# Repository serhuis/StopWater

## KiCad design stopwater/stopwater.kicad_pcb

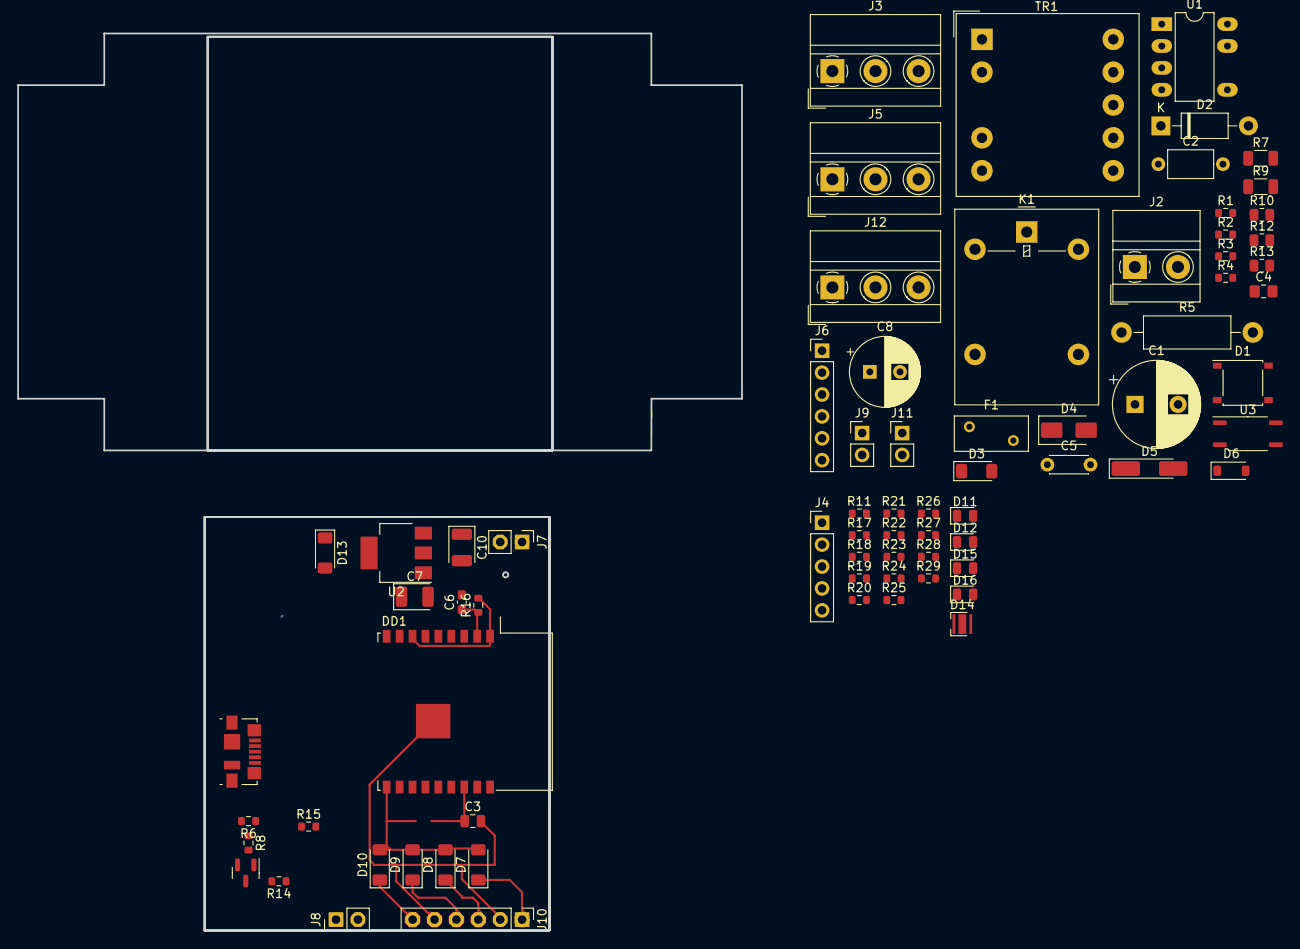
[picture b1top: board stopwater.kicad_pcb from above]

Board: 2 copper layers, 84.0 x 104.1 mm, 74 parts (0 on the bottom side), 57 nets.

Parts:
C1: 10u 400v; CP_Radial_D10.0mm_P5.00mm
C2: 2.2n; C_Axial_L5.1mm_D3.1mm_P7.50mm_Horizontal
C3: 1u; C_0805_2012Metric
C4: C_Polarized_Small; C_0805_2012Metric_Pad1.18x1.45mm_HandSolder
C5: C_Polarized_Small; C_Disc_D4.3mm_W1.9mm_P5.00mm
C6: 0.1u; C_0603_1608Metric_Pad1.08x0.95mm_HandSolder
C7, C10: 10u; CP_EIA-3528-15_AVX-H
C8: 200u 16v; CP_Radial_D8.0mm_P3.50mm
D1: ABS10; Diode_Bridge_Diotec_ABS
D2: 1N4937; D_DO-41_SOD81_P10.16mm_Horizontal
D3, D7, D8, D9, D10, D13: LL4148; D_MiniMELF
D4: SS14; D_SMA
D5: 8v2; D_MiniMELF_Handsoldering
D6: MMSD4148; D_SOD-123
D11, D12: "SENS_1"; LED_0805_2012Metric
D14: LED_Dual_AAK; LED_Cree-XB
D15: "SENS_3"; LED_0805_2012Metric
D16: "SENS_4"; LED_0805_2012Metric
DD1: ESP32c3-WROOM-02; ESP-WROOM-02
F1: 8.2R; Fuse_BelFuse_0ZRE0005FF_L8.3mm_W3.8mm
J1: USB_B_Micro; USB_Micro-B_Molex_47346-0001
J2: ~220; TerminalBlock_MetzConnect_Type011_RT05502HBWC_1x02_P5.00mm_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
J3, J5, J12: Out; TerminalBlock_MetzConnect_Type011_RT05503HBWC_1x03_P5.00mm_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
J4: Conn_01x05; PinHeader_1x05_P2.54mm_Vertical
J6: Conn_01x06_Pin; PinHeader_1x06_P2.54mm_Vertical
J7, J9: Conn_01x02_Pin; PinHeader_1x02_P2.54mm_Vertical
J8, J11: Conn_01x02_Socket; PinHeader_1x02_P2.54mm_Vertical
J10: Conn_01x06_Socket; PinHeader_1x06_P2.54mm_Vertical
K1: G5LE-1; Relay_SPDT_Omron-G5LE-1
Q1: BC847; SOT-23
R1, R2, R3, R4, R14: 3.3k; R_0603_1608Metric
R5: 200k; R_Axial_DIN0411_L9.9mm_D3.6mm_P15.24mm_Horizontal
R6: 330; R_0603_1608Metric
R7, R9: 1M; R_1206_3216Metric
R8, R11, R16, R17, R18, R19, R20, R21, R22, R23, R24, R25, R26, R27, R28, R29: 10k; R_0603_1608Metric
R10: 10k; R_0805_2012Metric
R12: 330; R_0805_2012Metric
R13: 680; R_0805_2012Metric
R15: 1k; R_0603_1608Metric
TR1: FAT_74082
U1: TNY268P; PowerIntegrations_PDIP-8B
U2: LD1117S33TR_SOT223; SOT-223-3_TabPin2
U3: TLP181; SOIC-4_4.55x3.7mm_P2.54mm

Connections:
+3.3V: C3.1, C7.1, DD1.1 (3V3), R11.1, R16.2, R17.1, R18.1, R19.1, R20.1, R21.1, R22.1, R23.1, R24.1, R25.1, R26.1, R27.1, R28.1, R29.1, U2.2 (VO)
+12V: C8.1 (plus), D4.1 (K), D5.1 (K), D6.1 (K), D6.2 (A), J8.1, J9.1, J9.2, J11.1, K1.2, K1.5, R1.1, R2.1, R3.1, R4.1
/+12: C10.1, D13.1 (K), J7.1, U2.3 (VI)
/IO_0: D7.2 (A), DD1.18 (IO0), R17.2
/IO_1: D8.2 (A), DD1.17 (IO1), R18.2
/IO_2: DD1.16 (IO2), R19.2
/IO_3: D9.2 (A), DD1.15 (IO3), R20.2
/IO_4: DD1.3 (IO4), R6.2, R15.2, R21.2
/IO_5: D11.1 (K), DD1.4 (IO5), R22.2
/IO_6: D12.1 (K), DD1.5 (IO6), R23.2
/IO_7: D15.1 (K), DD1.6 (IO7), R24.2
/IO_8: D16.1 (K), DD1.7 (IO8), R25.2
/IO_9: DD1.8 (IO9), J4.2, R26.2
/IO_10: D10.2 (A), DD1.10 (IO10)
/SENSOR_1: D7.1 (K), J10.1
/SENSOR_2: D8.1 (K), J10.3
/SENSOR_3: D9.1 (K), J10.4
/SENSOR_4: D10.1 (K), J10.6
/USB_DN: DD1.13 (IO18), J1.2 (D-)
/USB_DP: DD1.14 (IO19), J1.3 (D+)
/power/SENSOR_1: J3.1, J6.1, R1.2
/power/SENSOR_2: J3.3, J6.3, R2.2, R3.2
/power/SENSOR_3: J5.1, J6.4
/power/SENSOR_4: J5.3, J6.6, R4.2
GND: C3.2, C6.2, C7.2, C10.2, D14.3 (K), DD1.9 (GND), DD1.19 (GND), J1.5 (GND), J1.6 (Shield), J3.2, J4.3, J5.2, J6.2, J6.5, J7.2, J10.2, J10.5, J11.2, Q1.2 (E), R8.1, R13.2, U2.1 (GND), U3.3
unnamed: C1.2 (minus), C4.2 (minus), D1.2 (-), TR1.1, U1.2 (S), U1.3 (S), U1.7 (S), U1.8 (S), U3.4
unnamed: C1.1 (plus), C2.2, C5.2 (minus), D1.1 (+), R5.2, R7.2, TR1.5
unnamed: C4.1 (plus), R10.2, U1.1 (BP)
unnamed: C5.1 (plus), C8.2 (minus), TR1.10
unnamed: D1.3, F1.2
unnamed: D2.2 (A), TR1.4, U1.5 (D)
unnamed: C2.1, D2.1 (K), R5.1
unnamed: D3.2 (A), TR1.2
unnamed: D3.1 (K), R10.1
unnamed: D4.2 (A), TR1.6
unnamed: D5.2 (A), R12.2
unnamed: D11.2 (A), R11.2
unnamed: D12.2 (A), R27.2
unnamed: D13.2 (A), J1.1 (VBUS)
unnamed: D14.1 (A1), R15.1
unnamed: D14.2 (A2), R14.1
unnamed: D15.2 (A), R28.2
unnamed: D16.2 (A), R29.2
unnamed: C6.1, DD1.2 (EN), J4.1, R16.1
unnamed: DD1.11 (RXD), J4.4
unnamed: DD1.12 (TXD), J4.5
unnamed: F1.1, J2.1
unnamed: D1.4, J2.2
unnamed: J8.2, Q1.3 (C), R14.2
unnamed: J12.1, K1.4
unnamed: J12.2, K1.1
unnamed: J12.3, K1.3
unnamed: Q1.1 (B), R6.1, R8.2
unnamed: R7.1, R9.2
unnamed: R12.1, R13.1, U3.1
unnamed: TR1.7, TR1.9
unnamed: R9.1, U1.4 (EN/UV), U3.6

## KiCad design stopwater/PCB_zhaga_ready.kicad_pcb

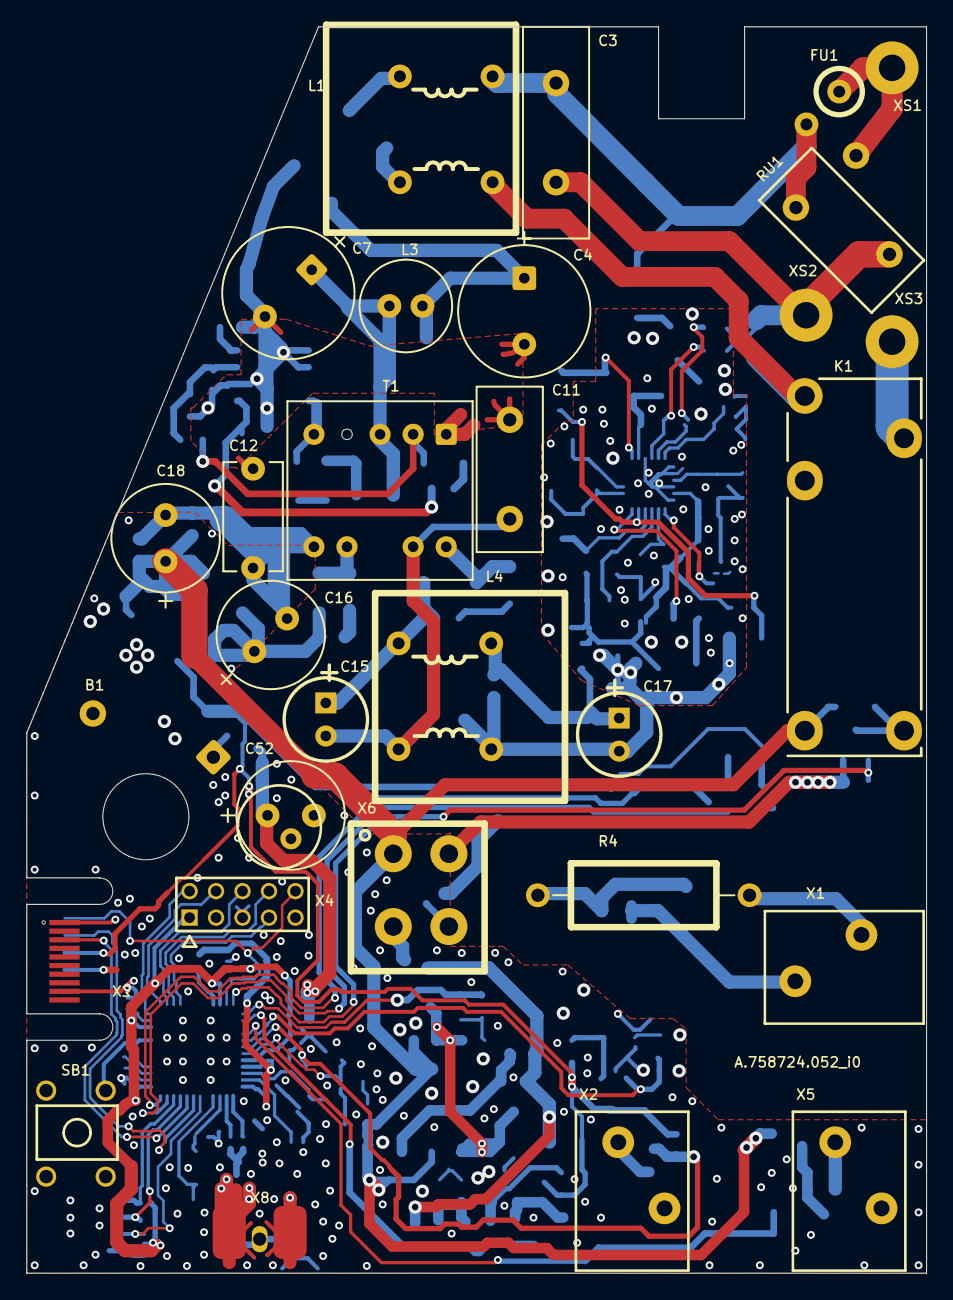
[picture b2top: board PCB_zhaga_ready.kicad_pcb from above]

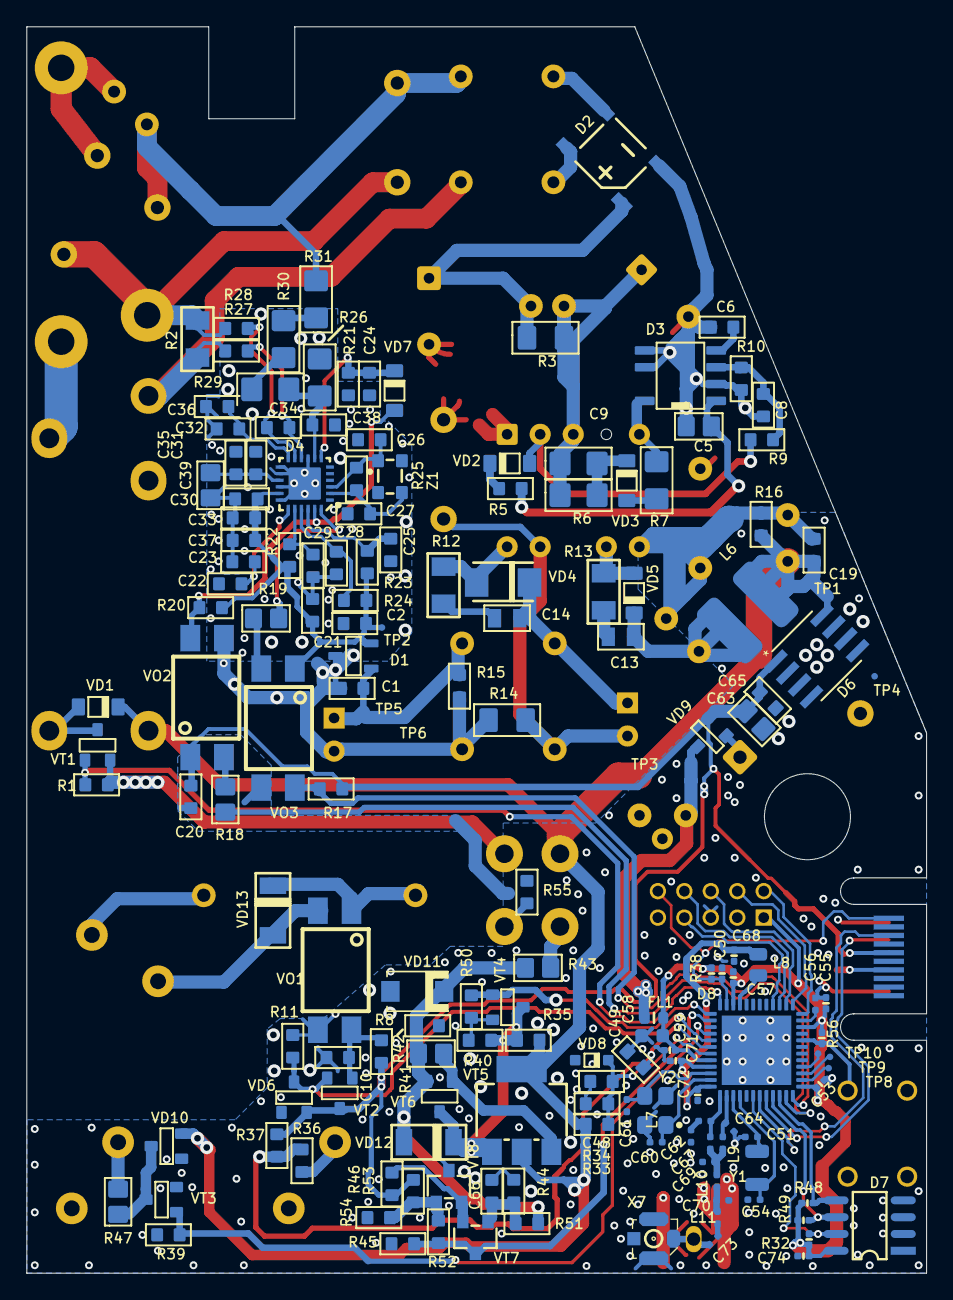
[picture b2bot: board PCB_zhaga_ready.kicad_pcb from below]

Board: 2 copper layers, 68.0 x 94.2 mm, 192 parts (162 on the bottom side), 105 nets.

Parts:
B1: BR-1225/VCN
C1, C6, C8, C34, C38, C49: 10nF 0603; 0603
C2: 22u 0603; 0603
C3: 1000pF 300VAC; L16W5 V
C4, C7: 4.7uF 400V; D10P5L12
C5: 10uF 35V; 0805
C9: 1000pF 300VAC; 1206
C10: 470nF 0603; 0603
C11: 1000pF 300VAC; L12.5W5
C12: 1000pF 300VAC; L7.5W5H6P7.5
C13, C14: SMD 0805-1000пФ±5% 50В X7R; __Altium_Library_Footprints_Passive.PcbLib_0805
C15, C17: 100uF 10V; D6.3P2.5L11.5
C16, C18: 470uF 10V; D8P3.5L12
C19, C20, C21, C23, C24, C25, C28, C29, C33, C35, C36, C48, C65, C66: SMD 0603-0.1мкФ±10% 25В X7R; 0603
C22, C37: SMD 0603-0,022мкФ±10% 25В X7R; 0603
C26, C27: SMD 0603 18pF±5% 50В; 0603
C30, C31, C32: 150pF 0603; 0603
C39: 2.2u 0805; 0805
C50, C53, C55, C57, C59, C68, C71, C72, C74: Cap; rlc_402_smd
C51, C54, C60, C61, C73: 12pF; CAPC1005X60B2N
C52: SuperCAP 022F; D8P3.5L12_2
C56: 1uF; CAPC1005X60B2N
C58: 10uF; CAPC1608X90N
C62: 6.8pF; CAPC1005X60B2N
C63: 22u 0603; 0805
C64, C67, C70: 1pF; CAPC1005X60B2N
C69: DNM_0402; CAPC1005X60B2N
D1: AP7384-33SA-7; SOT23_3
D2: Диодная сборка MDB10S; MDB10S
D3: MP020A-5GS; SO-7
D4: STPM32; QFN24L
D6: L78L33ABD-TR; SO-8_STM
D7: Микросхема CAT24C64WI-G; __Altium_Library_Footprints_SO.PcbLib_SO8
D8: CC2640R2LRGZ; QFNFC50P700X700X100-49A2N
FL1: BLM18HE152SN1; FIL_BLM18HE152SN1DL
FU1: Предохранитель самовосстанвливающийся RXE-185; FRN01W
K1: RM12-3011-35-1024; RM12
L1, L4: Дроссель B82732-W2601-B030; TLF9UAH103WR23K1
L3: CW57-332K; CW57
L6: CW57-332K; L0504
L7, L9: 2.4nH; INDC1005X60B2N
L8: 10uH; INDC2012X150L
L10, L11: 2nH; INDC1005X60B2N
R1, R11, R15, R16, R17, R20, R21, R22, R23, R24, R33, R34, R39, R50, R55: 0603 4.75K 1%; 0603
R2: SMD 1206-22 кОм±5%; __Altium_Library_Footprints_Passive.PcbLib_1206
R3, R14: 1206 4.75K; 1206
R4: 220K 2W; RSS2WH
R5: 0603 10 1%; 0603
R6, R7: 120K 0.5W; 1206
R8: 0603 200K 1%; 0603
R9, R10: 0603 43.2K 1%; 0603
R12, R13: SMD 1206-100 Ом±1%; __Altium_Library_Footprints_Passive.PcbLib_1206
R18, R19, R41, R43, R47: 0805 560 Ом 1%; 0805
R25: RC0603JR-071ML; 0603
R26: CMA02040X4700GB300; 1206
R27, R28: 0603 1K 1%; 0603
R29, R30, R31: SMM02040C2703FB300; 1206
R32, R38, R48, R49, R56: Resistor; rlc_402_smd
R35, R36, R37, R40, R42, R44, R45, R46, R51, R52, R53, R54: 0603 100K ±1%; 0603
RU1: V10E320P
SB1: Выключатель SWT-16; BUTTON
T1: TS7W-4.32-14.61-8.63; TS5W
TP1, TP2, TP3, TP4, TP5, TP6, TP8, TP9, TP10: Тестовая точка; TP0.5
VD1, VD3, VD5, VD7: ES1JFL; SOD123
VD2: BAV3004W; SOD123
VD4: Диод SS110; SMAE
VD6, VD10: BAT54S; SOT23_3
VD8: Супрессор GBLC03C; SOD323
VD9: BAT54C; SOT23_3
VD11: Супрессор SMAJ12A-TR; __Altium_Library_Footprints_DO.PcbLib_DO214AC
VD12, VD13: Диод LL4148; __Altium_Library_Footprints_SOD.PcbLib_SOD80
VO1, VO2, VO3: FOD817B3SD
VT1, VT3, VT4: DMN65D8L-7; SOT23_3
VT2, VT6: BC847C; SOT23_3
VT5: Транзистор BCP56-16T1; __Altium_Library_Footprints_SOT.PcbLib_SOT223
VT7, VT8: Транзистор BC857C; __Altium_Library_Footprints_SOT.PcbLib_SOT23
X1, X2, X5: KLEMM2; DG250-3.5-02P-11-00A
X3: X_20_2MM; TEST con
X4: X_10_2MM; X_10_2MM_Primary
X6: X_IDC_1_4; 10127820-0422LF
X7: 2337019-1; 0734120114
X8: 2337019-1; RG174
XS1, XS2, XS3: Отв.на плате; Pad 1mm2
Y1: 32.768kHz; XTAL_FC-135N
Y2: 24MHz; OSCCC250X320X60-4L
Z1: SJK-7U-16.00-16-30-80-A-30; SSCP32X25

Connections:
+3.3V: C20.1, C63.1, C65.1, D6.1, R8.2, R17.2, R37.2, R46.1, R53.1, TP3.1, VD6.2, VD9.2, VO2.1, VT2.3, X3.10
+3.3Vpm: C2.1, C21.2, C30.1, C33.2, C37.2, D1.2, D4.17, R20.1, R22.2, R23.2, R24.2, TP2.1, VO3.1
+5Vpm: C1.2, C17.1, D1.1, L4.4, R15.1, TP5.1
COM: FU1.1, XS1.1
DALI RX: D8.38, R45.1, R52.2, VT7.3
DALI TX: D8.37, R50.1, VT4.1
DCDC_SW: D8.33, L8.1
DIO4_SCL: D7.6, D8.9, R49.1
DIO5_SDA: D7.5, D8.10, R48.1
DIO8_MISO: D8.14, TP8.1
DIO9_MOSI: D8.15, TP9.1
DIO10_SCLK: D8.16, TP10.1
DIO14_BTN2: D8.20, R56.1, SB1.1
DIO16_TDO: D8.26, X4.6
DIO17_TDI: D8.27, X4.8
DIO18_RTS/SWO: D8.28, X4.7
DIO29_Analog: C49.2, D8.42, R36.2, R37.1
DIO30_Analog: C48.1, D8.43, R33.1, R34.2, VD8.2
GNDA: B1.2, C10.1, C12.1, C16.2, C18.2, C19.2, C20.2, C48.2, C49.1, C50.2, C51.2, C52.2, C53.2, C54.2, C55.2, C56.2, C57.2, C58.2, C59.2, C60.2, C61.2, C62.2, C63.2, C64.1, C65.2, C66.2, C68.2, C69.2, C70.1, C71.2, C72.2, C74.2, D6.2, D6.3, D6.6, D6.7, D7.2, D7.3, D7.4, D8.49, R1.2, R11.1, R16.2, R34.1, R39.2, R40.2, R42.2, R44.2, R45.2, R50.2, R54.2, R55.2, SB1.2, T1.6, TP4.1, VD6.1, VD8.1, VD10.1, VD11.1, VO1.3, VO3.3, VT1.2, VT3.2, VT4.2, VT8.3, X2.2, X3.1, X3.14, X3.17, X4.3, X4.5, X4.9, X5.2, X6.2, X7.1, X7.2, X7.3, X8.1, X8.2, Y2.2, Y2.4
GNDpm: C1.1, C2.2, C3.2, C17.2, C21.1, C22.2, C23.2, C24.1, C25.2, C26.2, C27.1, C28.2, C29.2, C30.2, C31.1, C32.2, C33.1, C35.2, C36.1, C37.1, C38.1, C39.1, D1.3, D4.9, D4.13, D4.14, D4.16, D4.18, D4.25, L4.3, R2.2, R14.2, R15.2, R21.2, R26.1, R28.1, RU1.1, TP6.1, VO2.3, XS2.1, Z1.2, Z1.4
JTAG_TCK: D8.25, X4.4
JTAG_TMS: D8.24, X4.2
MovRX: D8.7, X3.6
MovTX: D8.8, X3.5
NRST: C50.1, D8.35, R38.2, X3.2, X4.10
NetB1_1: B1.1, VD9.1
NetC3_1: C3.1, FU1.2, L1.2, R31.2, RU1.2
NetC4_1: C4.1, D2.1, L3.1, R3.1
NetC4_2: C4.2, C5.2, C6.1, C7.2, C8.1, C11.2, C12.2, D2.2, D3.2, D3.5, D3.6, R10.2, T1.1
NetC5_1: C5.1, D3.1, R5.2
NetC6_2: C6.2, D3.4
NetC7_1: C7.1, C9.1, L3.2, R3.2, R6.1, T1.3
NetC8_2: C8.2, D3.3, R9.2, R10.1
NetC9_2: C9.2, R6.2, VD3.2
NetC10_2: C10.2, R8.1, VO1.4, VT2.1
NetC11_1: C11.1, C15.2, L4.2, R14.1, T1.9
NetC13_1: C13.1, R13.2
NetC13_2: C13.2, C16.1, L6.1, VD5.2
NetC14_1: C14.1, R12.2
NetC14_2: C14.2, C15.1, L4.1, VD4.2
NetC22_1: C22.1, C23.1, D4.19
NetC24_2: C24.2, D4.7, R21.1, VD7.2
NetC25_1: C25.1, D4.22, R23.1
NetC26_1: C26.1, D4.3, R25.2, Z1.1
NetC27_2: C27.2, D4.2, R25.1, Z1.3
NetC28_1: C28.1, D4.21, R24.1
NetC29_1: C29.1, D4.20, R22.1
NetC31_2: C31.2, C35.1, C39.2, D4.15
NetC32_1: C32.1, C36.2, D4.12
NetC34_1: C34.1, D4.11, R28.2
NetC34_2: C34.2, D4.10, R27.2
NetC38_2: C38.2, D4.8, R26.2, R29.1
NetC51_1: C51.1, D8.3, Y1.1
NetC54_1: C54.1, D8.4, Y1.2
NetC56_1: C56.1, D8.23
NetC60_1: C60.1, D8.47, Y2.1
NetC61_1: C61.1, D8.46, Y2.3
NetC62_1: C62.1, L7.2
NetC64_2: C64.2, D8.2, L9.1
NetC66_1: C66.1, R44.1, R51.1, VT7.1
NetC67_1: C67.1, C69.1, L9.2, L10.1
NetC67_2: C67.2, D8.1, L7.1
NetC70_2: C70.2, L10.2, L11.1
NetC73_1: C73.1, L11.2
NetC73_2: C73.2, X7.4, X8.4
NetD2_3: D2.3, L1.3
NetD2_4: D2.4, L1.4
NetD3_7: D3.7, R7.2, T1.5
NetD4_23: D4.23, R20.2, VD7.1, VO2.4
NetD4_24: D4.24, R19.2
NetK1_1: K1.1, VD1.1, VT1.3
NetK1_4: K1.4, XS3.1
NetK1_5: K1.5, L1.1, R2.1, R27.1
NetR4_1: R4.1, X1.2
NetR4_2: R4.2, VD13.2, VO1.1
NetR5_1: R5.1, VD2.2
NetR7_1: R7.1, VD3.1
NetR9_1: R9.1, T1.2, VD2.1
NetR12_1: R12.1, T1.10, VD4.1
NetR13_1: R13.1, T1.7, VD5.1
NetR18_2: R18.2, VO2.2
NetR19_1: R19.1, VO3.2
NetR29_2: R29.2, R30.1
NetR30_2: R30.2, R31.1
NetR35_2: R35.2, R40.1, VD12.2, VT4.3, VT5.1, VT6.3
NetR36_1: R36.1, X2.1
NetR41_1: R41.1, VT5.3, VT6.1
NetR41_2: R41.2, R42.1, R43.1, R51.2, VD11.2, VD12.1, VT6.2
NetR46_2: R46.2, VT7.2, VT8.2
NetR47_1: R47.1, VD10.3, VT3.3
NetR52_1: R52.1, R53.2, R54.1, VT8.1
NetR55_1: R55.1, X6.4
NetVD13_1: VD13.1, VO1.2, X1.1
PHS: D8.41, R11.2, VD6.3, VT2.2
PM_RX: D8.12, R17.1, VO3.4
PM_TX: D8.11, R18.1
PO1: R47.2, X5.1
PO2: R43.2, X6.3
PWM: D8.40, R39.1, VT3.1
REL: D8.36, R1.1, VT1.1
VCC: C18.1, C19.1, D6.8, K1.2, L6.2, R16.1, R33.2, R35.1, TP1.1, VD1.2, VD10.2, VT5.2, VT5.4, X6.1
VDDR: C68.1, C71.1, C72.1, D8.45, D8.48, L8.2
VDDS: C53.1, C55.1, C57.1, C58.1, C59.1, C74.1, D7.8, D8.13, D8.22, D8.34, D8.44, FL1.1, R32.2, R38.1, R48.2, R49.2, R56.2, X4.1
WMCU_VDD: C52.1, FL1.2, VD9.3
WP: D7.7, D8.6, R32.1

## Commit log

2023-06-02 Added files
2023-11-07 added some schematics
